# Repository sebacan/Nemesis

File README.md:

# Nemesis

Este un proiect hardware,finalist in cadrul Innovation Labs Bucharest 2016. 

Proiect ce a participat si la Sesiunea de Comunicări Științifice Studențești 2016,Politehnica București. 

Se bazează pe colectarea datelor de interes dintr-o centrală/uzină/fabrică si trasmiterea acestora catre un centru de comandă. 

Ne folosim de modulele XBee/ZigBee pentru a forma o rețea mesh în care dispozitivele comunică între ele. 

Datele obținute sunt mai apoi centralizare si urmărite. 

Avantaje:
Ușurință în instalare și mentenanță.

Protocol de comunicație standardizat pe frecvențele 2.4 Ghz,433 Mhz.

Monitorizare în timp real.

Consum și costuri reduse.

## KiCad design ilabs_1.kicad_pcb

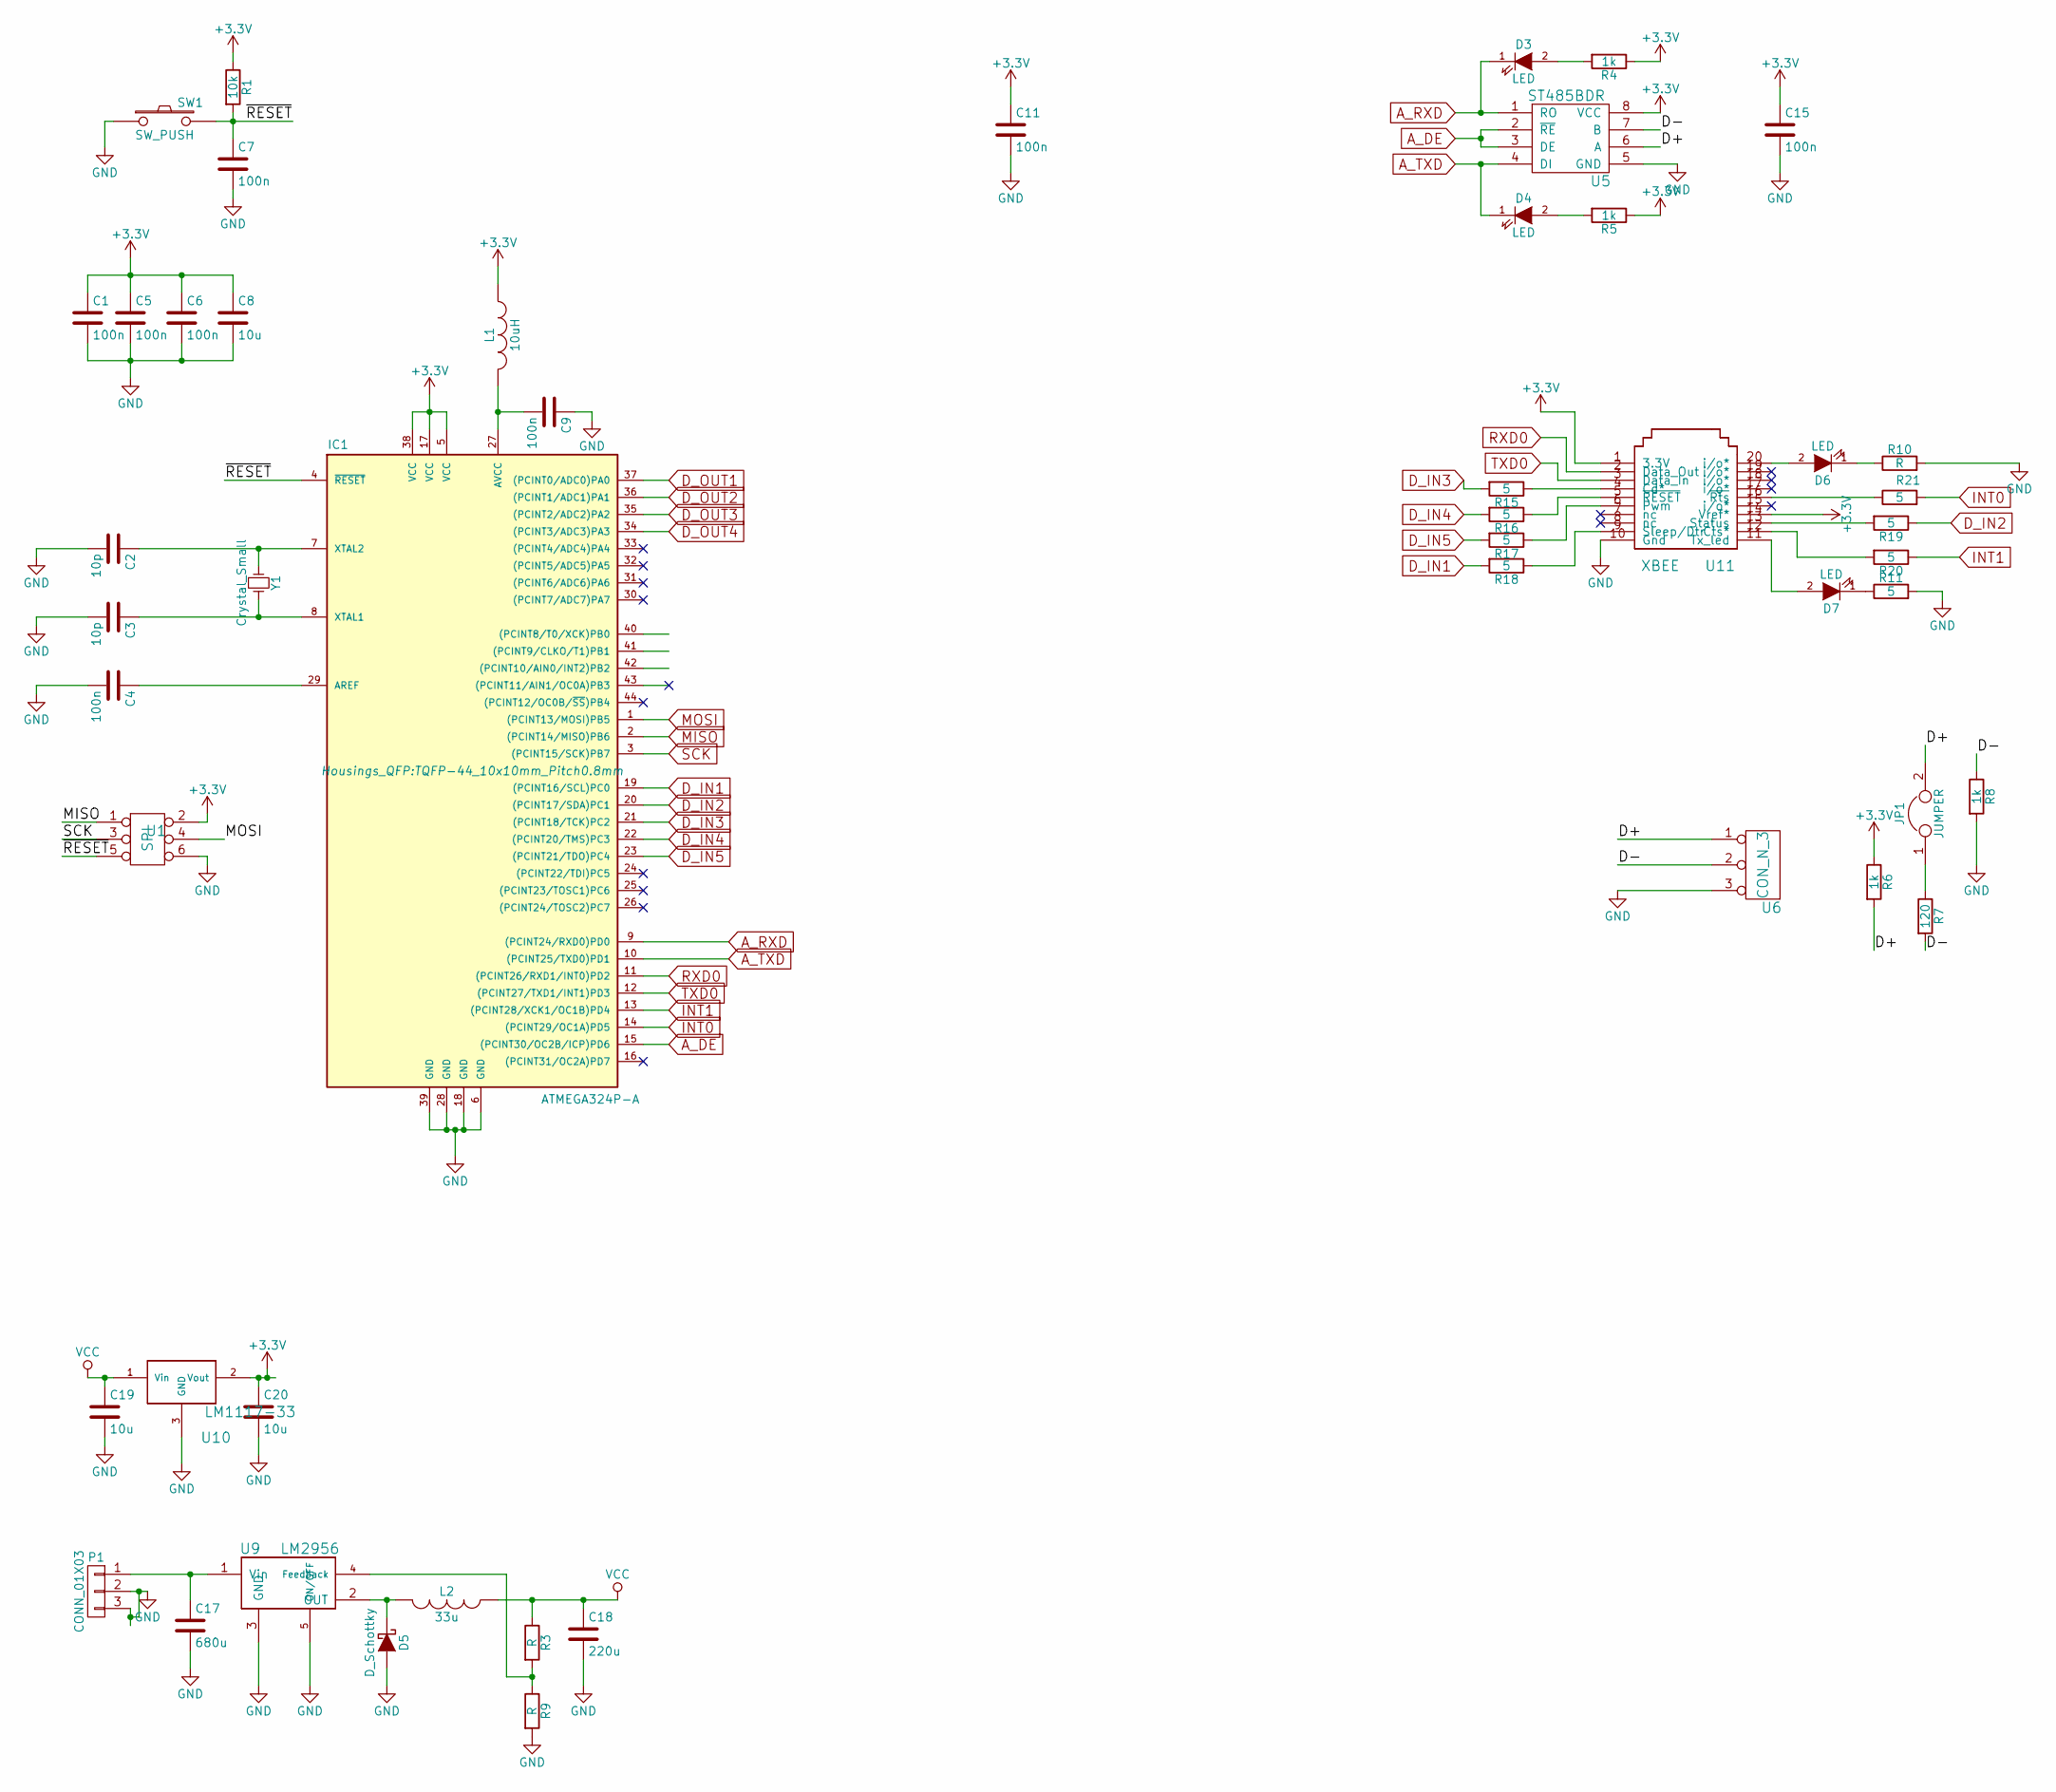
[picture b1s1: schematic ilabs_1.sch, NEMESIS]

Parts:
C1, C4, C5, C6, C7, C9, C11, C15: 100n; C_0805_HandSoldering
C2, C3: 10p; C_0805_HandSoldering
C8, C19, C20: 10u; C_0805_HandSoldering
C17: 680u; C_0805_HandSoldering
C18: 220u; C_0805_HandSoldering
D3, D4, D6, D7: LED; LED-5MM
D5: D_Schottky; DO-214AB_Handsoldering
IC1: ATMEGA324P-A; TQFP-44_10x10mm_Pitch0.8mm
JP1: JUMPER; Pin_Header_Angled_1x02
L1: 10uH; Neosid_Inductor_SM-NE30_SMD1210
L2: 33u; Neosid_Inductor_Ms95
P1: CONN_01X03; bornier3
R1: 10k; R_0805_HandSoldering
R3, R9, R10: R; R_0805_HandSoldering
R4, R5, R6, R8: 1k; R_0805_HandSoldering
R7: 120; R_0805_HandSoldering
R11, R15, R16, R17, R18, R19, R20, R21: 5; R_0805_HandSoldering
SW1: SW_PUSH
U1: SPI; Pin_Header_Angled_2x03
U5: ST485BDR; SOIC-8_3.9x4.9mm_Pitch1.27mm
U6: CON_N_3; bornier3
U9: LM2956; TO-263-5Lead
U10: LM1117-33; SOT-223
U11: XBEE
Y1: Crystal_Small; HC-18UV

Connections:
+3V3: C1.1, C5.1, C6.1, C8.1, C11.1, C15.1, C20.1, IC1.5 (VCC), IC1.17 (VCC), IC1.38 (VCC), L1.1, R1.1, R4.1, R5.1, R6.1, U1.2, U5.8 (VCC), U10.2 (Vout), U11.1 (3.3V), U11.14 (Vref*)
/D+: JP1.2, R6.2, U5.6 (A), U6.1
/D-: R7.2, R8.1, U5.7 (B), U6.2
/~RESET: C7.1, IC1.4 (~RESET), R1.2, SW1.2, U1.5
A_DE: IC1.15 ((PCINT30/OC2B/ICP)PD6), U5.2 (~RE), U5.3 (DE)
A_RXD: D3.1 (K), IC1.9 ((PCINT24/RXD0)PD0), U5.1 (RO)
A_TXD: D4.1 (K), IC1.10 ((PCINT25/TXD0)PD1), U5.4 (DI)
D_IN1: IC1.19 ((PCINT16/SCL)PC0), R18.2
D_IN2: IC1.20 ((PCINT17/SDA)PC1), R19.1
D_IN3: IC1.21 ((PCINT18/TCK)PC2), R15.2
D_IN4: IC1.22 ((PCINT20/TMS)PC3), R16.2
D_IN5: IC1.23 ((PCINT21/TDO)PC4), R17.2
D_OUT1: IC1.37 ((PCINT0/ADC0)PA0)
D_OUT2: IC1.36 ((PCINT1/ADC1)PA1)
D_OUT3: IC1.35 ((PCINT2/ADC2)PA2)
D_OUT4: IC1.34 ((PCINT3/ADC3)PA3)
GND: C1.2, C2.2, C3.2, C4.2, C5.2, C6.2, C7.2, C8.2, C9.1, C11.2, C15.2, C17.2, C18.2, C19.2, C20.2, D5.2 (A), IC1.6 (GND), IC1.18 (GND), IC1.28 (GND), IC1.39 (GND), P1.2, P1.3, R8.2, R9.2, R10.2, R11.2, SW1.1, U1.6, U5.5 (GND), U6.3, U9.3 (GND), U9.5 (ON/OFF), U10.3 (GND), U11.10 (Gnd)
INT0: IC1.14 ((PCINT29/OC1A)PD5), R21.2
INT1: IC1.13 ((PCINT28/XCK1/OC1B)PD4), R20.1
MISO: IC1.2 ((PCINT14/MISO)PB6), U1.1
MOSI: IC1.1 ((PCINT13/MOSI)PB5), U1.4
unnamed: C2.1, IC1.7 (XTAL2), Y1.1
unnamed: C3.1, IC1.8 (XTAL1), Y1.2
unnamed: C4.1, IC1.29 (AREF)
unnamed: C9.2, IC1.27 (AVCC), L1.2
unnamed: C17.1, P1.1, U9.1 (Vin)
unnamed: D3.2 (A), R4.2
unnamed: D4.2 (A), R5.2
unnamed: D5.1 (K), L2.2, U9.2 (OUT)
unnamed: D6.1 (K), R10.1
unnamed: D6.2 (A), U11.20 (i/o*)
unnamed: D7.1 (K), R11.1
unnamed: D7.2 (A), U11.11 (Tx_led)
unnamed: JP1.1, R7.1
unnamed: R3.2, R9.1, U9.4 (Feedback)
unnamed: R15.1, U11.4 (Cd*)
unnamed: R16.1, U11.5 (~RESET)
unnamed: R17.1, U11.6 (Pwm)
unnamed: R18.1, U11.9 (Sleep/Dtr)
unnamed: R19.2, U11.13 (Status)
unnamed: R20.2, U11.12 (Cts*)
unnamed: R21.1, U11.16 (~Rts)
RXD0: IC1.11 ((PCINT26/RXD1/INT0)PD2), U11.2 (Data_Out)
SCK: IC1.3 ((PCINT15/SCK)PB7), U1.3
TXD0: IC1.12 ((PCINT27/TXD1/INT1)PD3), U11.3 (Data_In)
VCC: C18.1, C19.1, L2.1, R3.1, U10.1 (Vin)

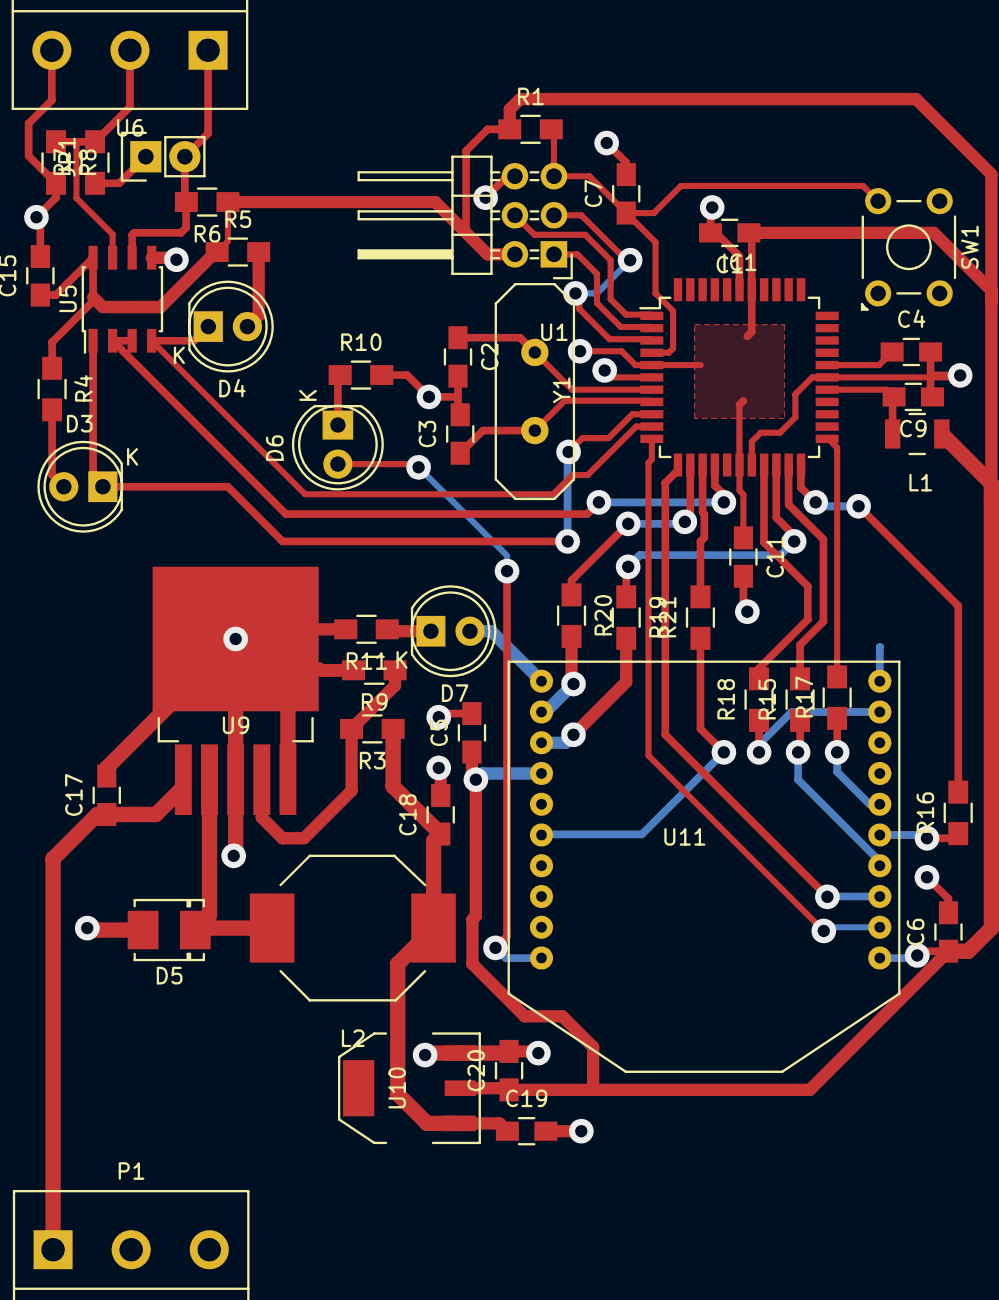
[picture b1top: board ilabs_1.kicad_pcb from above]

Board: 2 copper layers, 50 parts (1 on the bottom side), 42 nets.
